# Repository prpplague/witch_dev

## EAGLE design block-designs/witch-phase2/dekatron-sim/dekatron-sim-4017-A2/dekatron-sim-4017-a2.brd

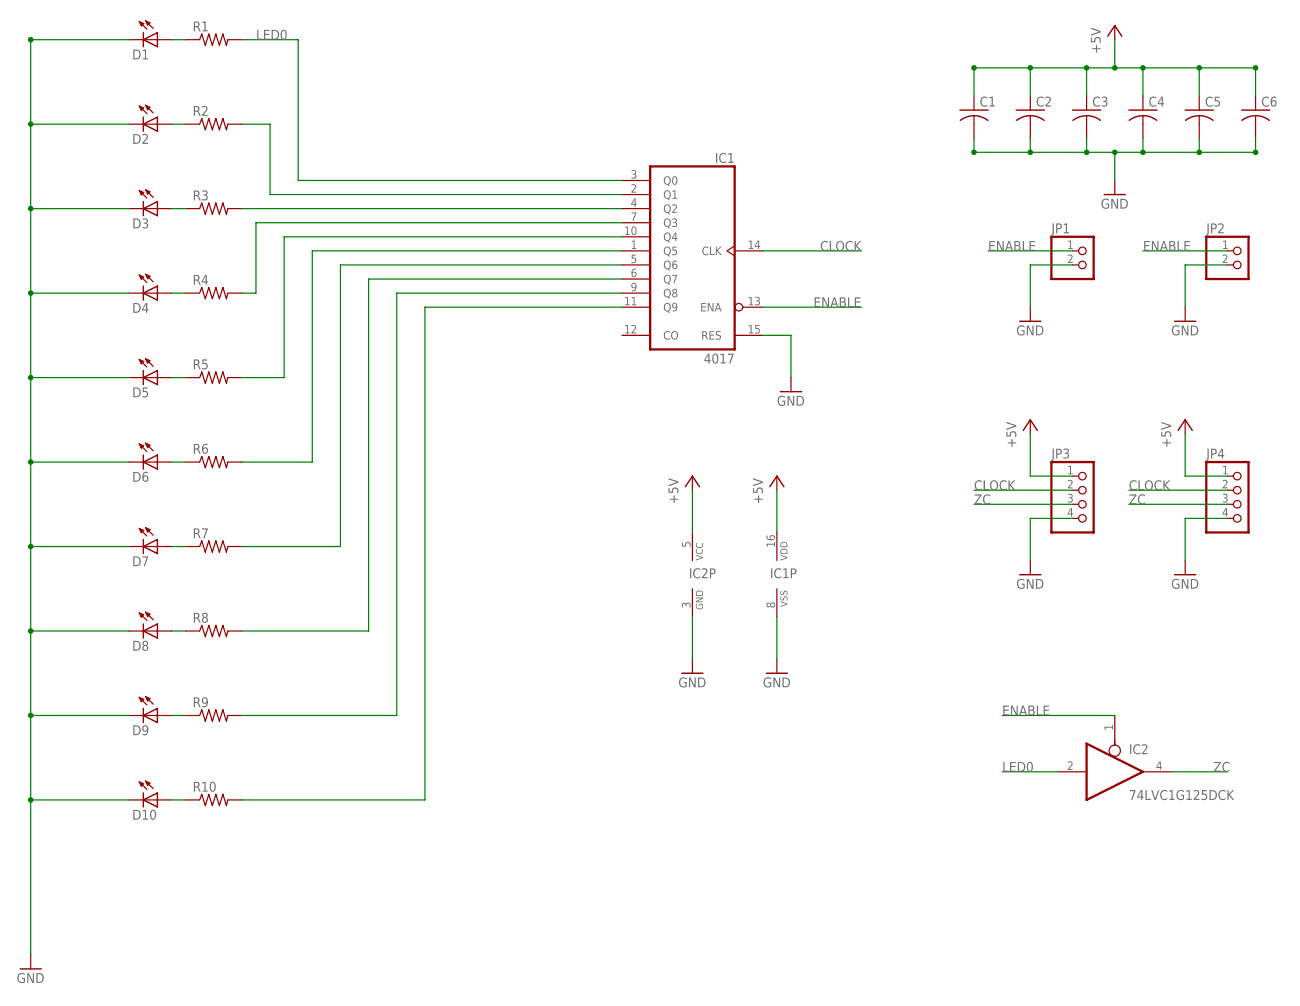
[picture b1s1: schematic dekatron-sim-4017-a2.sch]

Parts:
C1, C2, C3, C4, C5, C6: C-USC0805; C0805
D1, D2, D3, D4, D5, D6, D7, D8, D9, D10: RED; CHIP-LED0603
IC1: 4017; TSSOP16
IC2: 74LVC1G125DCK; SC70-5
JP1, JP2: PINHD-1X2; 1X02
JP3, JP4: PINHD-1X4; 1X04
R1, R2, R3, R4, R5, R6, R7, R8, R9, R10: R-US_R0603; R0603

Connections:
+5V: C1.1, C2.1, C3.1, C4.1, C5.1, C6.1, IC1.16 (VDD), IC2.5 (VCC), JP3.1, JP4.1
CLOCK: IC1.14 (CLK), JP3.2, JP4.2
ENABLE: IC1.13 (ENA), IC2.1 (OE), JP1.1, JP2.1
GND: C1.2, C2.2, C3.2, C4.2, C5.2, C6.2, D1.C, D2.C, D3.C, D4.C, D5.C, D6.C, D7.C, D8.C, D9.C, D10.C, IC1.8 (VSS), IC1.15 (RES), IC2.3 (GND), JP1.2, JP2.2, JP3.4, JP4.4
LED0: IC1.3 (Q0), IC2.2 (I), R1.2
LED1: IC1.2 (Q1), R2.2
LED3: IC1.7 (Q3), R4.2
LED4: IC1.10 (Q4), R5.2
LED5: IC1.1 (Q5), R6.2
LED6: IC1.5 (Q6), R7.2
LED7: IC1.6 (Q7), R8.2
LED8: IC1.9 (Q8), R9.2
LED9: IC1.11 (Q9), R10.2
unnamed: IC1.4 (Q2), R3.2
unnamed: D10.A, R10.1
unnamed: D9.A, R9.1
unnamed: D8.A, R8.1
unnamed: D7.A, R7.1
unnamed: D6.A, R6.1
unnamed: D5.A, R5.1
unnamed: D4.A, R4.1
unnamed: D3.A, R3.1
unnamed: D2.A, R2.1
unnamed: D1.A, R1.1
ZC: IC2.4 (O), JP3.3, JP4.3

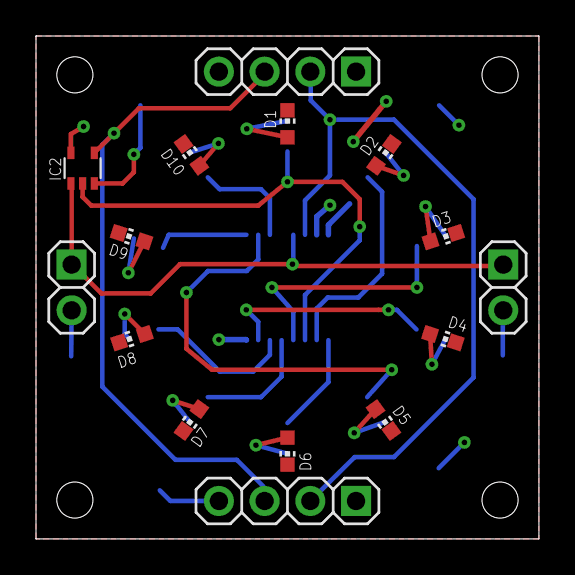
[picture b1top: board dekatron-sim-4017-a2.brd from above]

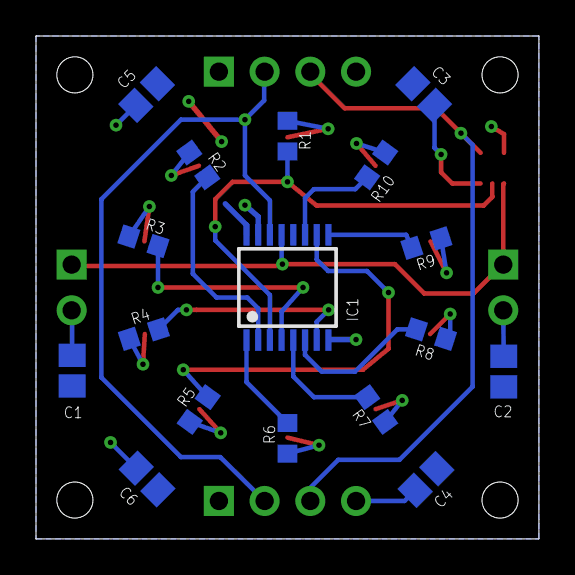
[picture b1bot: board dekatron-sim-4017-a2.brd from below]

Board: 2 copper layers, 27.9 x 27.9 mm, 32 parts (17 on the bottom side), 25 nets.

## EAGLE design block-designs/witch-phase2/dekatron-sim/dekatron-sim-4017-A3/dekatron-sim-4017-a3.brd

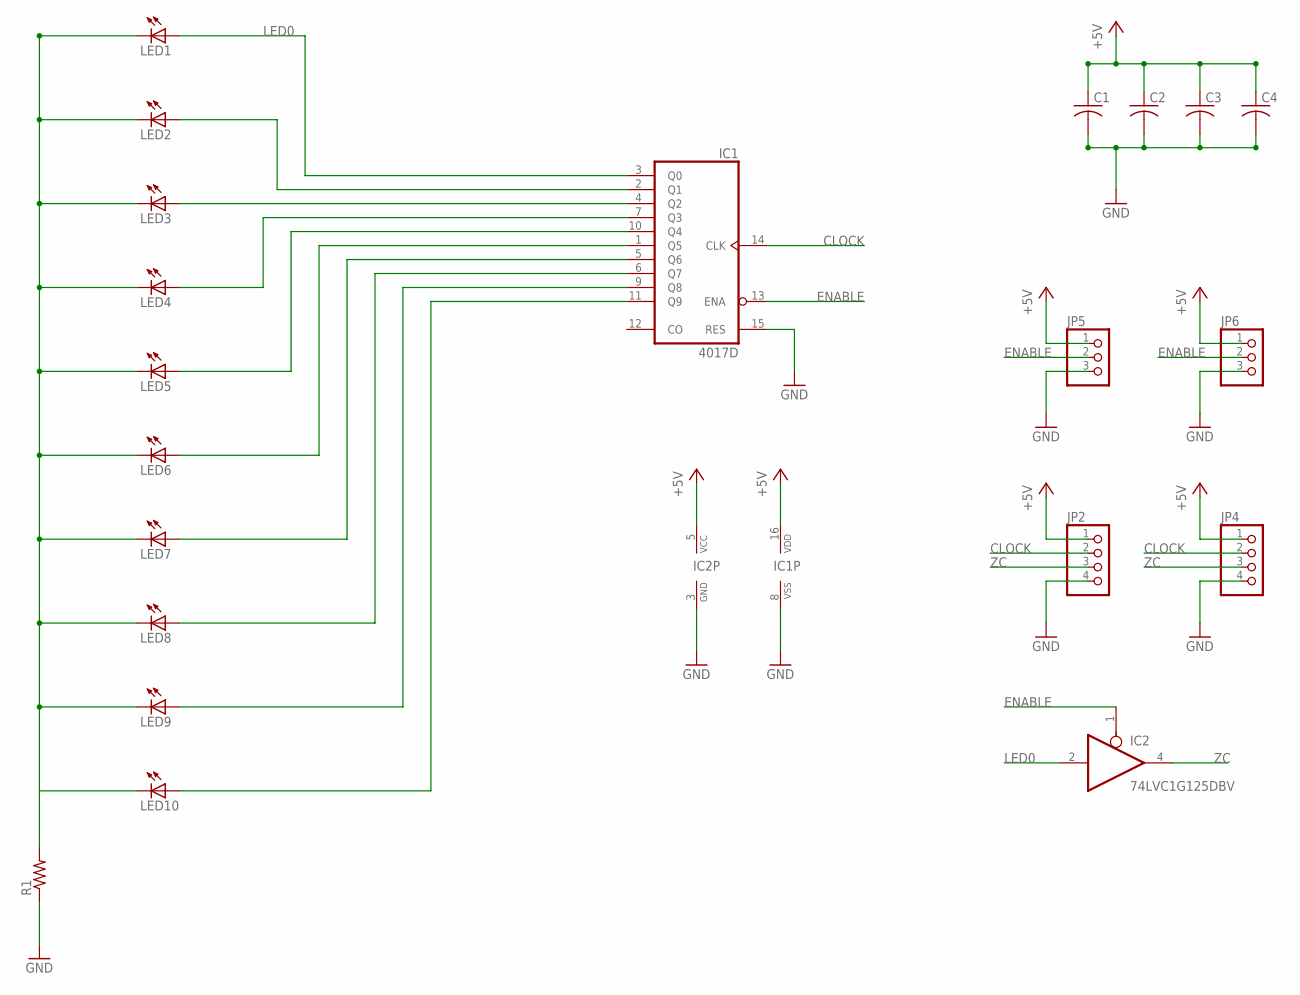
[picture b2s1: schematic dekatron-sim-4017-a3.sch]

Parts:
C1, C2, C3, C4: C-USC0805; C0805
IC1: 4017D; SO16
IC2: 74LVC1G125DBV; SOT23-5
JP2, JP4: PINHD-1X4; 1X04
JP5, JP6: PINHD-1X3; 1X03
LED1, LED2, LED3, LED4, LED5, LED6, LED7, LED8, LED9, LED10: RED; CHIP-LED0805
R1: R-US_R0805; R0805

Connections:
+5V: C1.1, C2.1, C3.1, C4.1, IC1.16 (VDD), IC2.5 (VCC), JP2.1, JP4.1, JP5.1, JP6.1
CLOCK: IC1.14 (CLK), JP2.2, JP4.2
ENABLE: IC1.13 (ENA), IC2.1 (OE), JP5.2, JP6.2
GND: C1.2, C2.2, C3.2, C4.2, IC1.8 (VSS), IC1.15 (RES), IC2.3 (GND), JP2.4, JP4.4, JP5.3, JP6.3, R1.1
LED0: IC1.3 (Q0), IC2.2 (I), LED1.A
LED1: IC1.2 (Q1), LED2.A
LED3: IC1.7 (Q3), LED4.A
LED4: IC1.10 (Q4), LED5.A
LED5: IC1.1 (Q5), LED6.A
LED6: IC1.5 (Q6), LED7.A
LED7: IC1.6 (Q7), LED8.A
LED8: IC1.9 (Q8), LED9.A
LED9: IC1.11 (Q9), LED10.A
LED_SINK: LED1.C, LED2.C, LED3.C, LED4.C, LED5.C, LED6.C, LED7.C, LED8.C, LED9.C, LED10.C, R1.2
unnamed: IC1.4 (Q2), LED3.A
ZC: IC2.4 (O), JP2.3, JP4.3

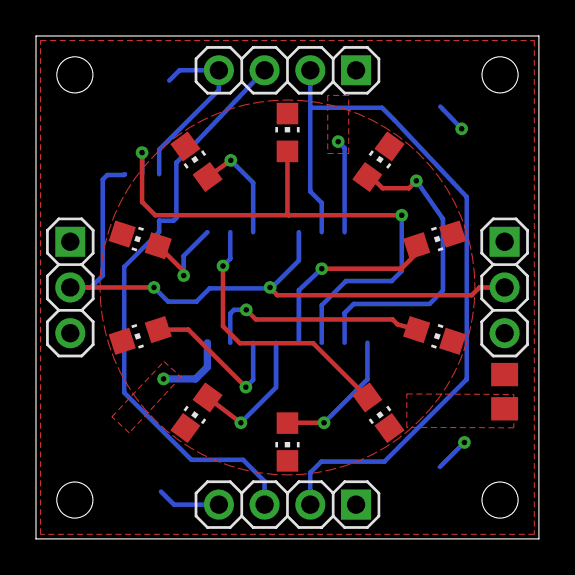
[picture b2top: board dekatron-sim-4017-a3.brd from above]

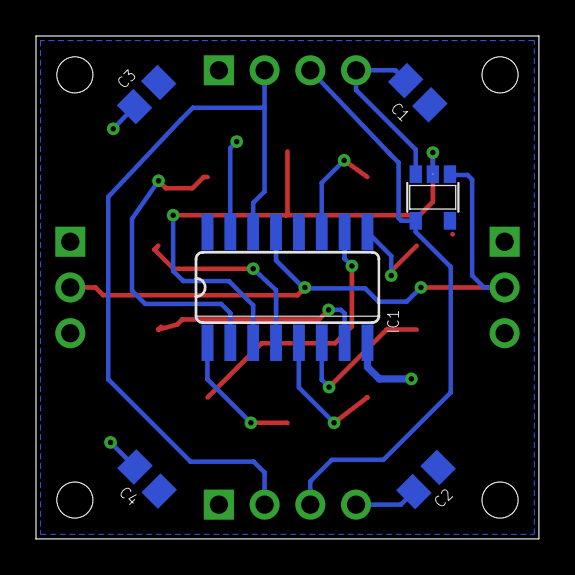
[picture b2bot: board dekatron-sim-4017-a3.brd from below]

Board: 2 copper layers, 27.9 x 27.9 mm, 21 parts (6 on the bottom side), 16 nets.

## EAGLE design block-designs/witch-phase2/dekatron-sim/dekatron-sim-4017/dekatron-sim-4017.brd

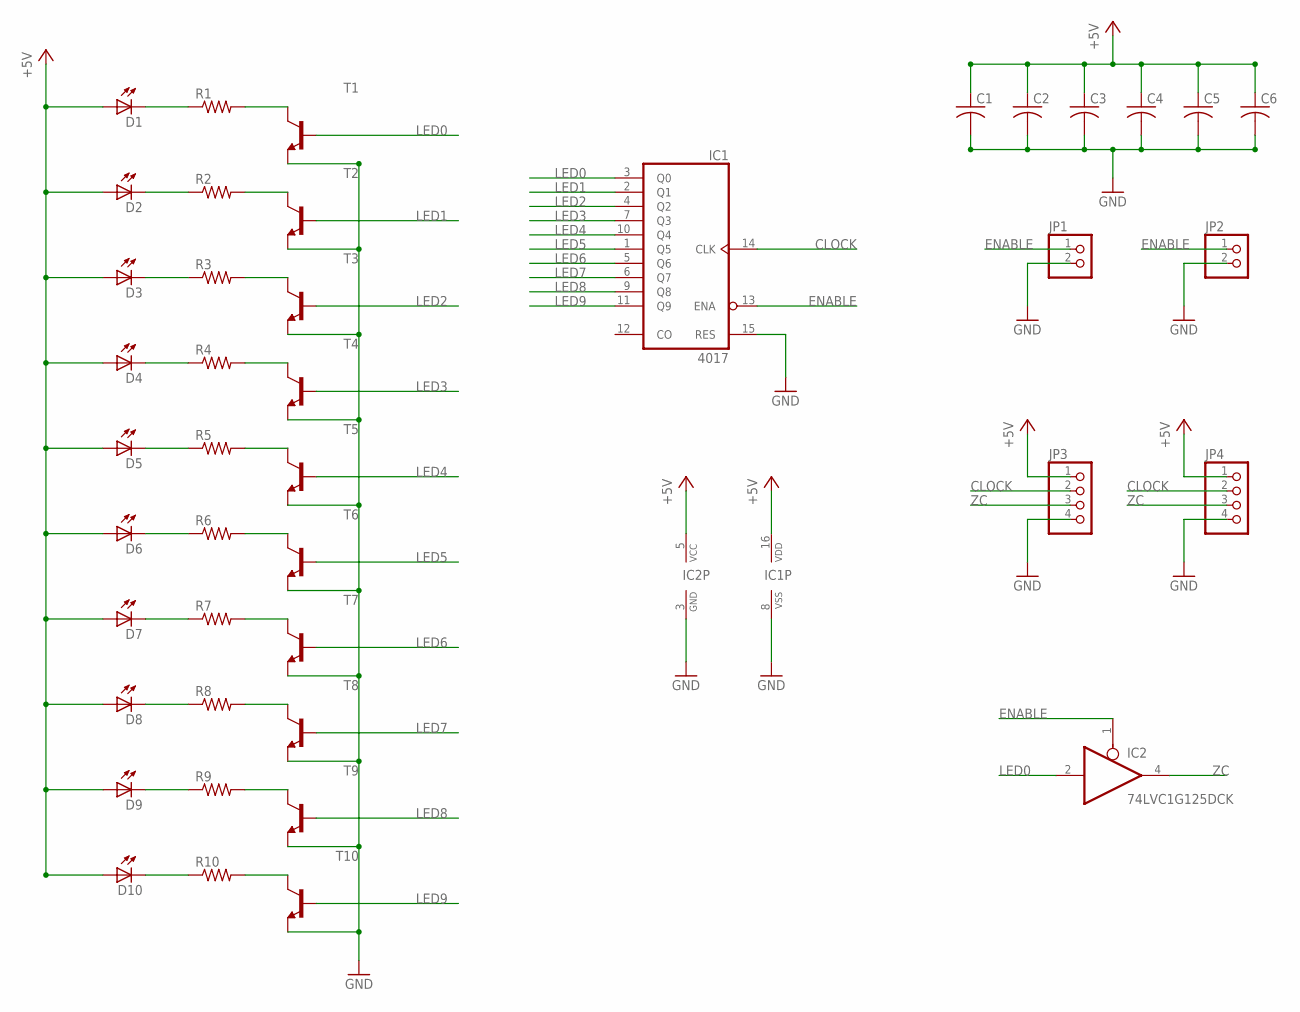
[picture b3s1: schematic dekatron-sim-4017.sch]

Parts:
C1, C2, C3, C4, C5, C6: C-USC0805; C0805
D1, D2, D3, D4, D5, D6, D7, D8, D9, D10: RED; CHIP-LED0603
IC1: 4017; TSSOP16
IC2: 74LVC1G125DCK; SC70-5
JP1, JP2: PINHD-1X2; 1X02
JP3, JP4: PINHD-1X4; 1X04
R1, R2, R3, R4, R5, R6, R7, R8, R9, R10: R-US_R0603; R0603
T1, T2, T3, T4, T5, T6, T7, T8, T9, T10: MMBT2222ALT1-NPN-SOT23-BEC; SOT23-BEC

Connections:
+5V: C1.1, C2.1, C3.1, C4.1, C5.1, C6.1, D1.A, D2.A, D3.A, D4.A, D5.A, D6.A, D7.A, D8.A, D9.A, D10.A, IC1.16 (VDD), IC2.5 (VCC), JP3.1, JP4.1
CLOCK: IC1.14 (CLK), JP3.2, JP4.2
ENABLE: IC1.13 (ENA), IC2.1 (OE), JP1.1, JP2.1
GND: C1.2, C2.2, C3.2, C4.2, C5.2, C6.2, IC1.8 (VSS), IC1.15 (RES), IC2.3 (GND), JP1.2, JP2.2, JP3.4, JP4.4, T1.E, T2.E, T3.E, T4.E, T5.E, T6.E, T7.E, T8.E, T9.E, T10.E
LED0: IC1.3 (Q0), IC2.2 (I), T1.B
LED1: IC1.2 (Q1), T2.B
LED2: IC1.4 (Q2), T3.B
LED3: IC1.7 (Q3), T4.B
LED4: IC1.10 (Q4), T5.B
LED5: IC1.1 (Q5), T6.B
LED6: IC1.5 (Q6), T7.B
LED7: IC1.6 (Q7), T8.B
LED8: IC1.9 (Q8), T9.B
LED9: IC1.11 (Q9), T10.B
unnamed: R10.2, T10.C
unnamed: R9.2, T9.C
unnamed: R8.2, T8.C
unnamed: D10.C, R10.1
unnamed: D9.C, R9.1
unnamed: D8.C, R8.1
unnamed: D7.C, R7.1
unnamed: R7.2, T7.C
unnamed: D6.C, R6.1
unnamed: R6.2, T6.C
unnamed: D5.C, R5.1
unnamed: R5.2, T5.C
unnamed: D4.C, R4.1
unnamed: R4.2, T4.C
unnamed: D3.C, R3.1
unnamed: R3.2, T3.C
unnamed: D2.C, R2.1
unnamed: R2.2, T2.C
unnamed: D1.C, R1.1
unnamed: R1.2, T1.C
ZC: IC2.4 (O), JP3.3, JP4.3

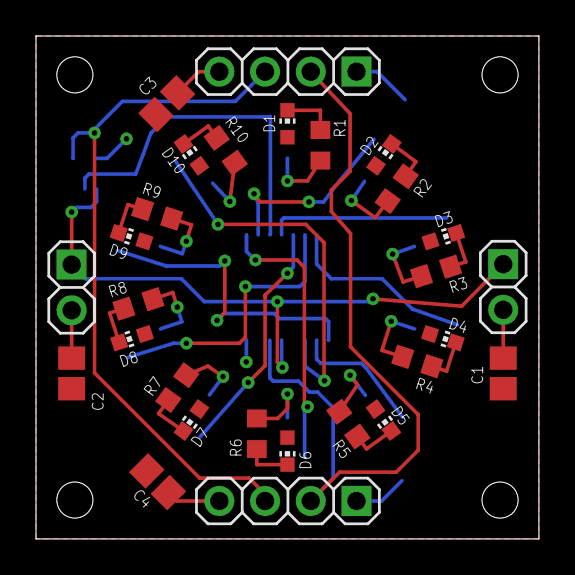
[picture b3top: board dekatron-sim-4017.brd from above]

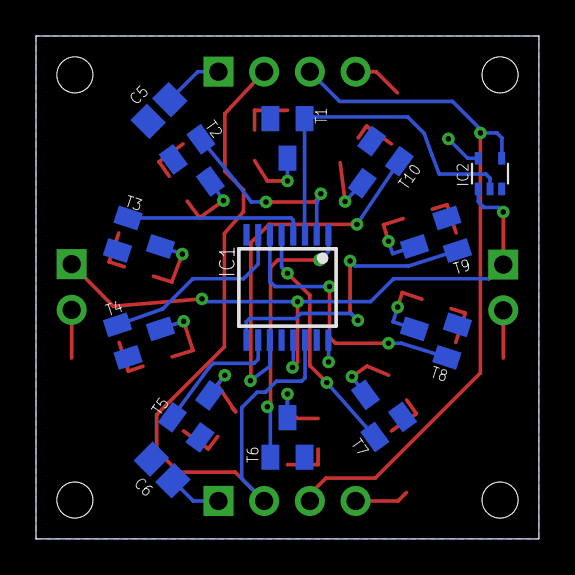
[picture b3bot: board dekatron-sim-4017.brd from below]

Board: 2 copper layers, 27.9 x 27.9 mm, 42 parts (14 on the bottom side), 35 nets.

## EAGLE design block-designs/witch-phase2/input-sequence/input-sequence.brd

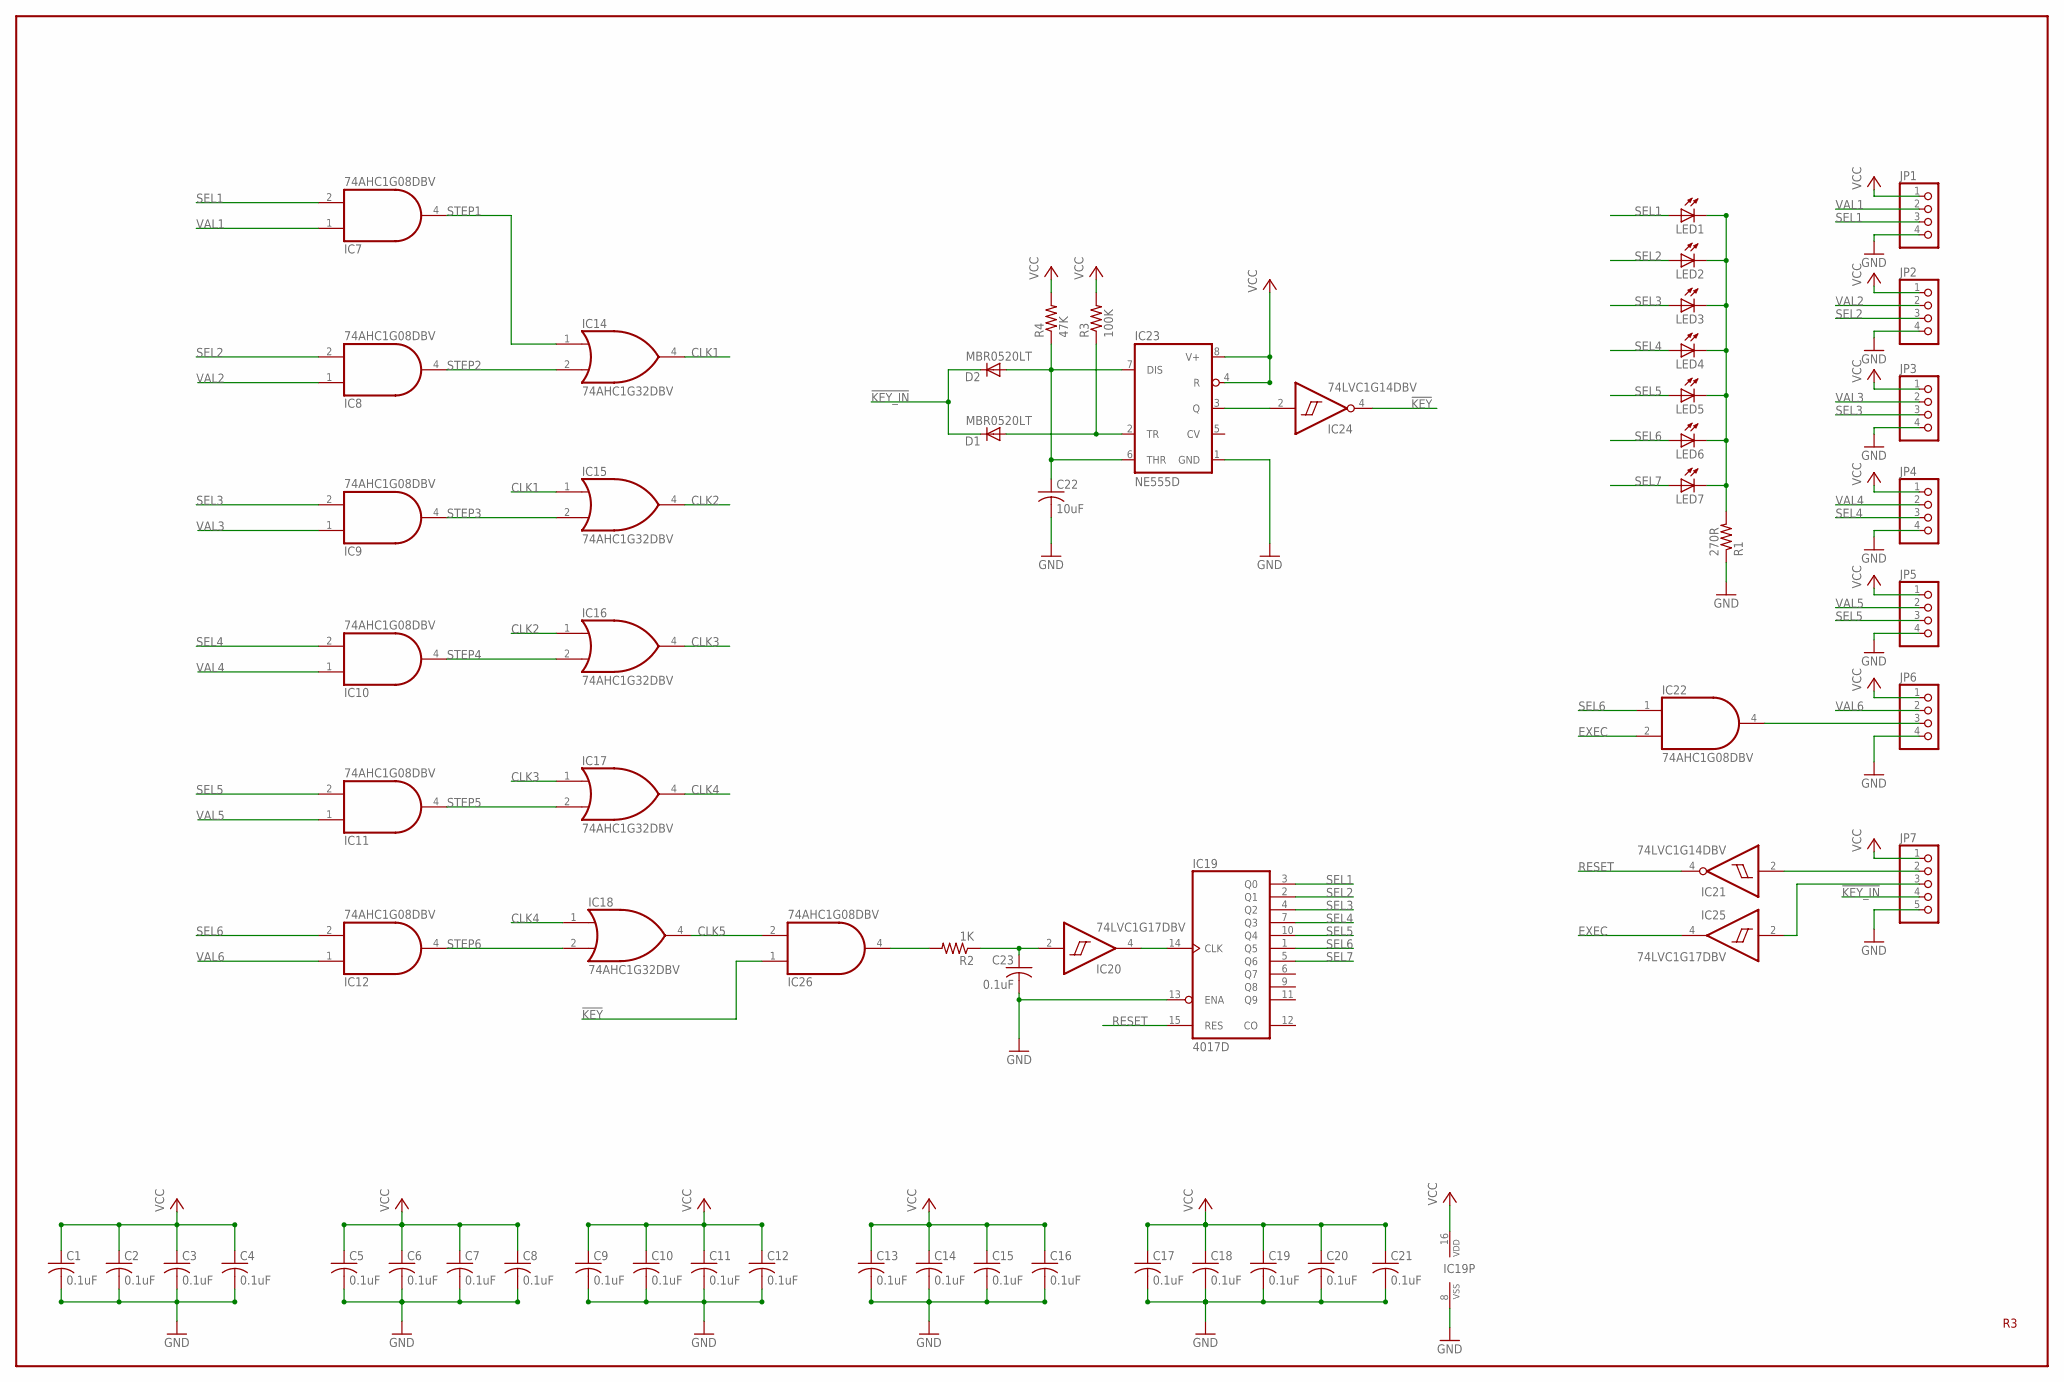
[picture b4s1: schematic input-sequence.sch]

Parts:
C1, C2, C3, C4, C5, C6, C7, C8, C9, C10, C11, C12, C13, C14, C15, C16, C17, C18, C19, C20, C21, C23: 0.1uF; C0603
C22: 10uF; C0805
D1, D2: MBR0520LT; SOD123
IC7, IC8, IC9, IC10, IC11, IC12, IC22, IC26: 74AHC1G08DBV; SOT23-5
IC14, IC15, IC16, IC17, IC18: 74AHC1G32DBV; SOT23-5
IC19: 4017D; SO16
IC20, IC25: 74LVC1G17DBV; SOT23-5
IC21, IC24: 74LVC1G14DBV; SOT23-5
IC23: NE555D; SO08
JP1, JP2, JP3, JP4, JP5, JP6: PINHD-1X4; 1X04
JP7: PINHD-1X5; 1X05
LED1, LED2, LED3, LED4, LED5, LED6, LED7: RED; CHIP-LED0805
R1: 270R; R0805
R2: 1K; R0805
R3: 100K; R0805
R4: 47K; R0805

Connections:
!CLEAR: IC21.2 (I), JP7.2
!KEY: IC24.4 (O), IC26.1 (I0)
!KEY_IN: D1.C, D2.C, JP7.4
CLK1: IC14.4 (O), IC15.1 (I0)
CLK2: IC15.4 (O), IC16.1 (I0)
CLK3: IC16.4 (O), IC17.1 (I0)
CLK4: IC17.4 (O), IC18.1 (I0)
CLK5: IC18.4 (O), IC26.2 (I1)
EXEC: IC22.2 (I1), IC25.4 (O)
GND: C1.2, C2.2, C3.2, C4.2, C5.2, C6.2, C7.2, C8.2, C9.2, C10.2, C11.2, C12.2, C13.2, C14.2, C15.2, C16.2, C17.2, C18.2, C19.2, C20.2, C21.2, C22.2, C23.2, IC7.3 (GND), IC8.3 (GND), IC9.3 (GND), IC10.3 (GND), IC11.3 (GND), IC12.3 (GND), IC14.3 (GND), IC15.3 (GND), IC16.3 (GND), IC17.3 (GND), IC18.3 (GND), IC19.8 (VSS), IC19.13 (ENA), IC20.3 (GND), IC21.3 (GND), IC22.3 (GND), IC23.1 (GND), IC24.3 (GND), IC25.3 (GND), IC26.3 (GND), JP1.4, JP2.4, JP3.4, JP4.4, JP5.4, JP6.4, JP7.5, R1.1
LED_SINK: LED1.C, LED2.C, LED3.C, LED4.C, LED5.C, LED6.C, LED7.C, R1.2
unnamed: IC22.4 (O), JP6.3
unnamed: IC19.14 (CLK), IC20.4 (O)
unnamed: C22.1, D2.A, IC23.6 (THR), IC23.7 (DIS), R4.1
unnamed: D1.A, IC23.2 (TR), R3.1
unnamed: IC23.3 (Q), IC24.2 (I)
unnamed: IC25.2 (I), JP7.3
unnamed: C23.1, IC20.2 (I), R2.1
unnamed: IC26.4 (O), R2.2
RESET: IC19.15 (RES), IC21.4 (O)
SEL1: IC7.2 (I1), IC19.3 (Q0), JP1.3, LED1.A
SEL2: IC8.2 (I1), IC19.2 (Q1), JP2.3, LED2.A
SEL3: IC9.2 (I1), IC19.4 (Q2), JP3.3, LED3.A
SEL4: IC10.2 (I1), IC19.7 (Q3), JP4.3, LED4.A
SEL5: IC11.2 (I1), IC19.10 (Q4), JP5.3, LED5.A
SEL6: IC12.2 (I1), IC19.1 (Q5), IC22.1 (I0), LED6.A
SEL7: IC19.5 (Q6), LED7.A
STEP1: IC7.4 (O), IC14.1 (I0)
STEP2: IC8.4 (O), IC14.2 (I1)
STEP3: IC9.4 (O), IC15.2 (I1)
STEP4: IC10.4 (O), IC16.2 (I1)
STEP5: IC11.4 (O), IC17.2 (I1)
STEP6: IC12.4 (O), IC18.2 (I1)
VAL1: IC7.1 (I0), JP1.2
VAL2: IC8.1 (I0), JP2.2
VAL3: IC9.1 (I0), JP3.2
VAL4: IC10.1 (I0), JP4.2
VAL5: IC11.1 (I0), JP5.2
VAL6: IC12.1 (I0), JP6.2
VCC: C1.1, C2.1, C3.1, C4.1, C5.1, C6.1, C7.1, C8.1, C9.1, C10.1, C11.1, C12.1, C13.1, C14.1, C15.1, C16.1, C17.1, C18.1, C19.1, C20.1, C21.1, IC7.5 (VCC), IC8.5 (VCC), IC9.5 (VCC), IC10.5 (VCC), IC11.5 (VCC), IC12.5 (VCC), IC14.5 (VCC), IC15.5 (VCC), IC16.5 (VCC), IC17.5 (VCC), IC18.5 (VCC), IC19.16 (VDD), IC20.5 (VCC), IC21.5 (VCC), IC22.5 (VCC), IC23.4 (R), IC23.8 (V+), IC24.5 (VCC), IC25.5 (VCC), IC26.5 (VCC), JP1.1, JP2.1, JP3.1, JP4.1, JP5.1, JP6.1, JP7.1, R3.2, R4.2

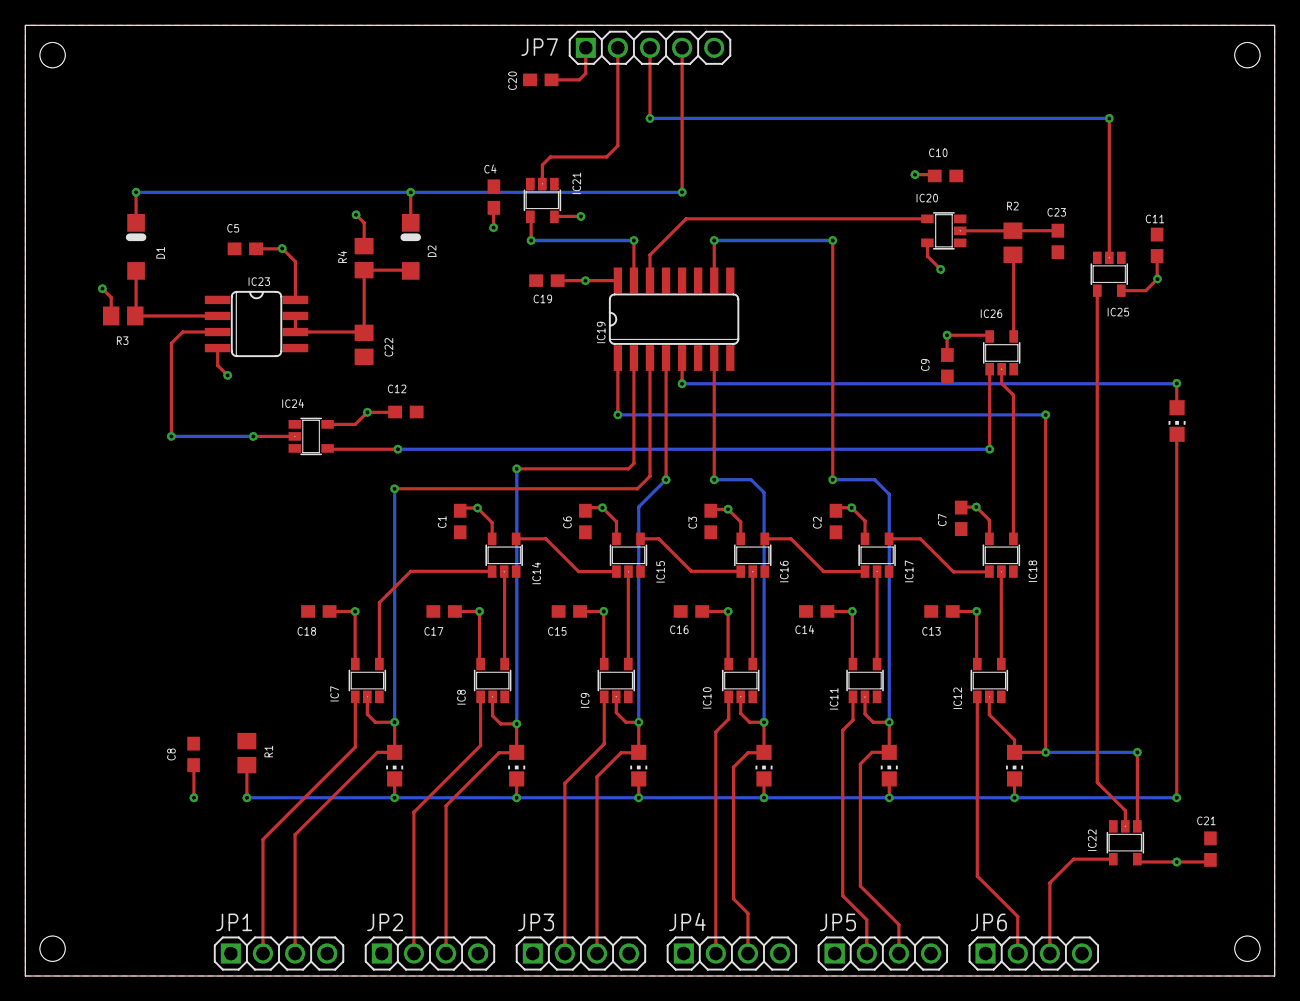
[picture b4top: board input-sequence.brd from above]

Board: 2 copper layers, 98.8 x 75.2 mm, 62 parts (0 on the bottom side), 40 nets.

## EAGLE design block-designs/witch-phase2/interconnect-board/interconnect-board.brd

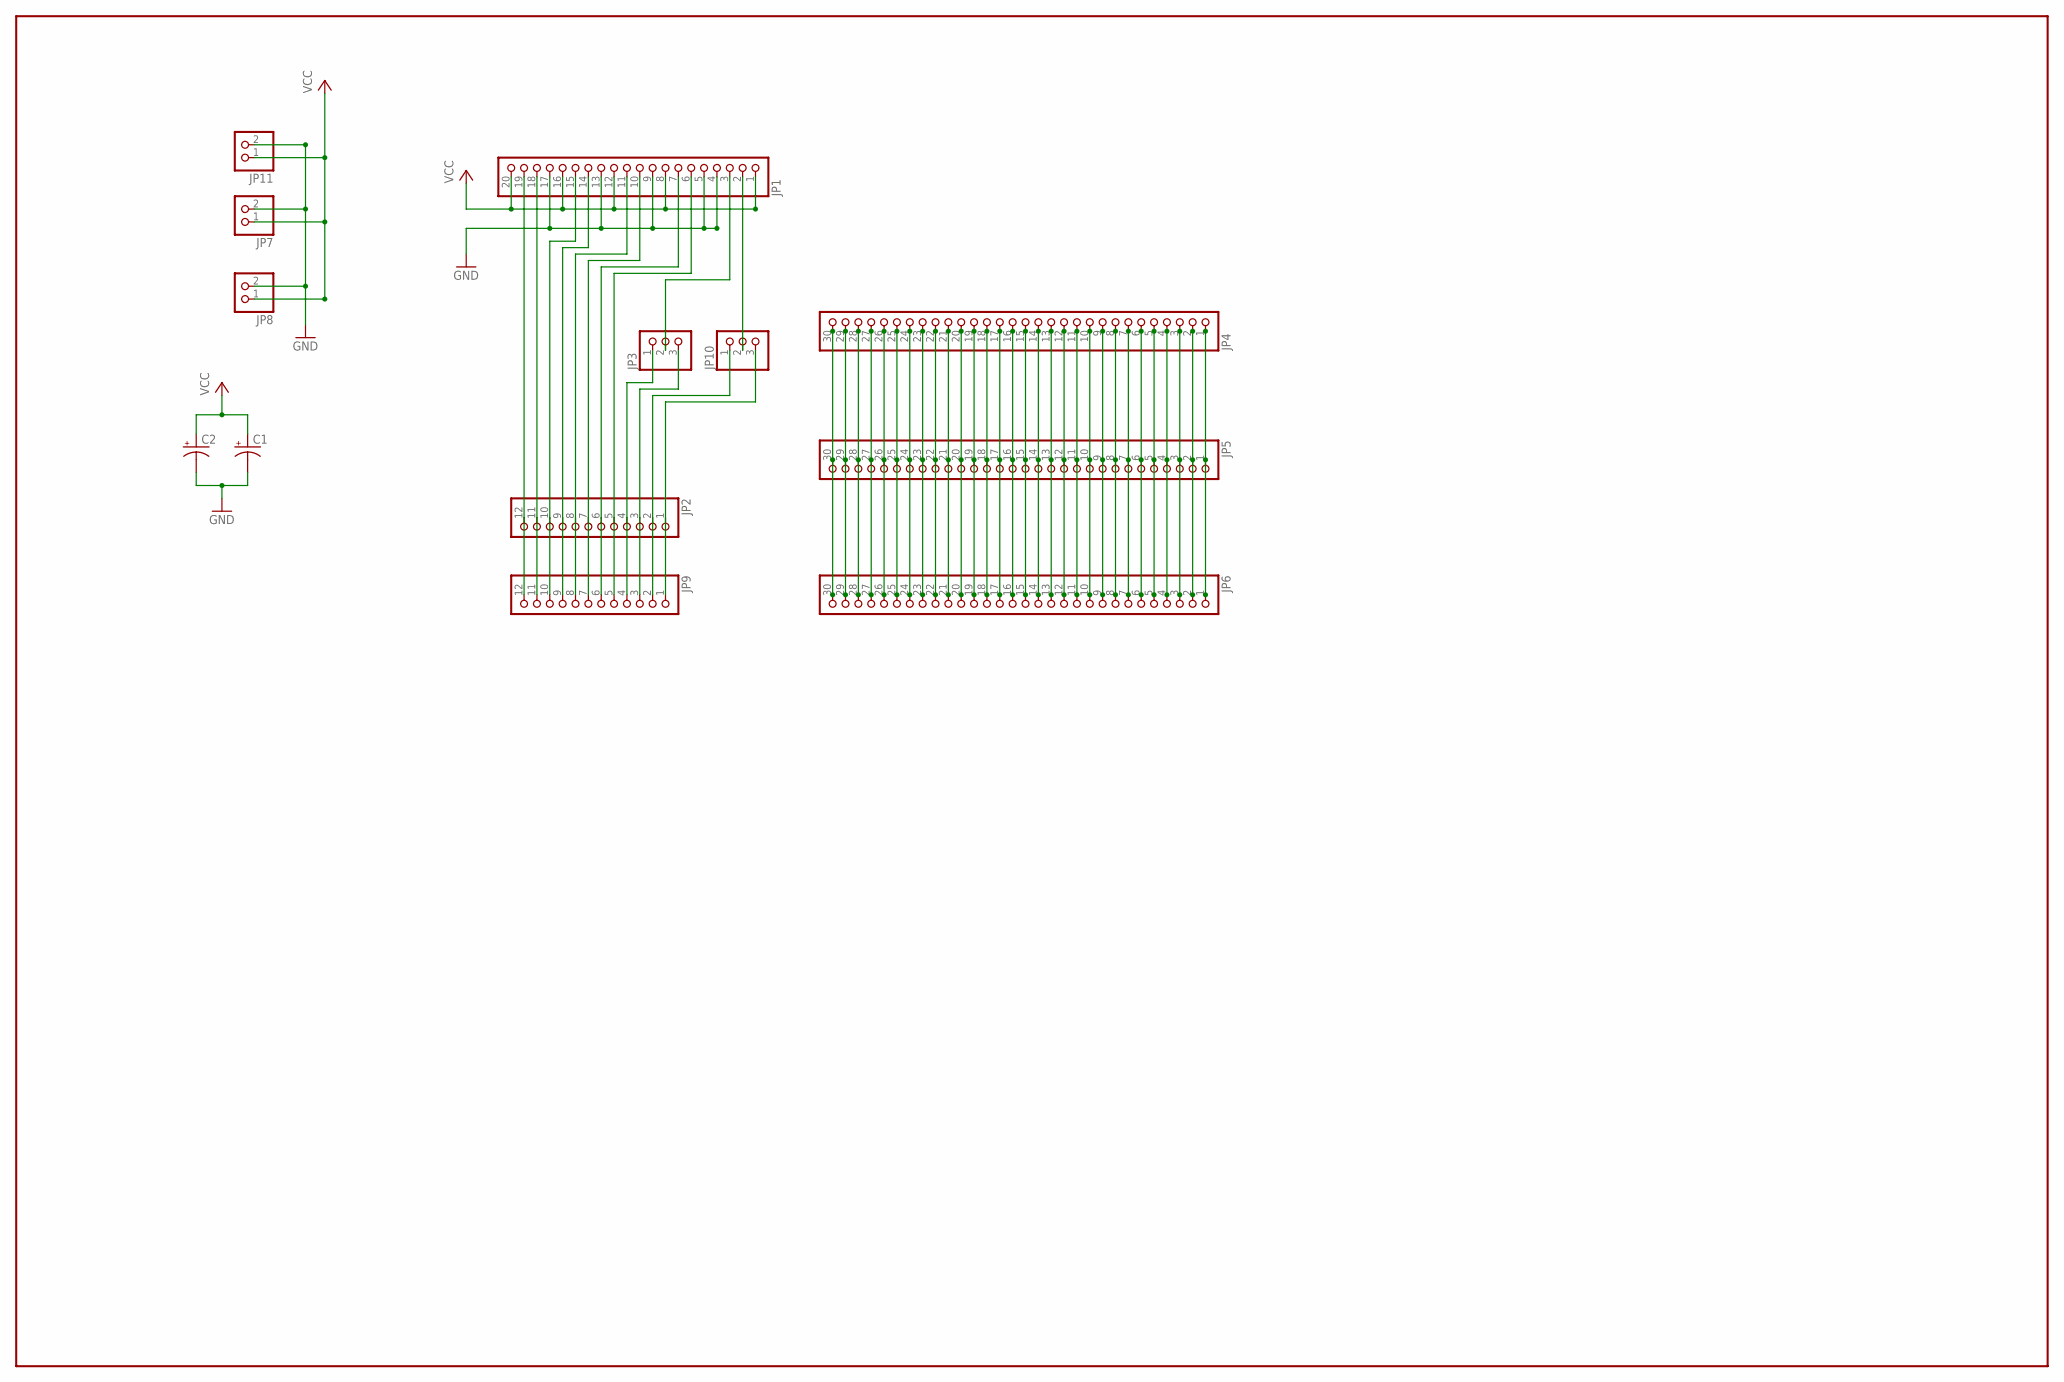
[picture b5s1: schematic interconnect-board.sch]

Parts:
C1, C2: CPOL-USE15-6AXIAL; E15-6
JP1: PINHD-1X20; 1X20
JP2, JP9: PINHD-1X12; 1X12
JP3, JP10: PINHD-1X3; 1X03
JP4, JP5, JP6: PINHD-1X30; 1X30
JP7, JP8, JP11: PINHD-1X2; 1X02

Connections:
GND: C1.-, C2.-, JP1.4, JP1.5, JP1.9, JP1.13, JP1.17, JP7.2, JP8.2, JP11.2
unnamed: JP4.30, JP5.30, JP6.30
unnamed: JP4.29, JP5.29, JP6.29
unnamed: JP4.28, JP5.28, JP6.28
unnamed: JP4.27, JP5.27, JP6.27
unnamed: JP4.26, JP5.26, JP6.26
unnamed: JP4.25, JP5.25, JP6.25
unnamed: JP4.24, JP5.24, JP6.24
unnamed: JP4.23, JP5.23, JP6.23
unnamed: JP4.22, JP5.22, JP6.22
unnamed: JP4.21, JP5.21, JP6.21
unnamed: JP4.20, JP5.20, JP6.20
unnamed: JP4.19, JP5.19, JP6.19
unnamed: JP4.18, JP5.18, JP6.18
unnamed: JP4.17, JP5.17, JP6.17
unnamed: JP4.16, JP5.16, JP6.16
unnamed: JP4.15, JP5.15, JP6.15
unnamed: JP4.14, JP5.14, JP6.14
unnamed: JP4.13, JP5.13, JP6.13
unnamed: JP4.12, JP5.12, JP6.12
unnamed: JP4.11, JP5.11, JP6.11
unnamed: JP4.10, JP5.10, JP6.10
unnamed: JP4.9, JP5.9, JP6.9
unnamed: JP4.8, JP5.8, JP6.8
unnamed: JP4.7, JP5.7, JP6.7
unnamed: JP4.6, JP5.6, JP6.6
unnamed: JP4.5, JP5.5, JP6.5
unnamed: JP4.4, JP5.4, JP6.4
unnamed: JP4.3, JP5.3, JP6.3
unnamed: JP4.2, JP5.2, JP6.2
unnamed: JP4.1, JP5.1, JP6.1
unnamed: JP1.19, JP2.12, JP9.12
unnamed: JP1.18, JP2.11, JP9.11
unnamed: JP1.15, JP2.10, JP9.10
unnamed: JP1.14, JP2.9, JP9.9
unnamed: JP1.11, JP2.8, JP9.8
unnamed: JP1.10, JP2.7, JP9.7
unnamed: JP1.7, JP2.6, JP9.6
unnamed: JP1.6, JP2.5, JP9.5
unnamed: JP2.4, JP3.1, JP9.4
unnamed: JP2.3, JP3.3, JP9.3
unnamed: JP2.2, JP9.2, JP10.1
unnamed: JP1.3, JP3.2
unnamed: JP1.2, JP10.2
unnamed: JP2.1, JP9.1, JP10.3
VCC: C1.+, C2.+, JP1.1, JP1.8, JP1.12, JP1.16, JP1.20, JP7.1, JP8.1, JP11.1

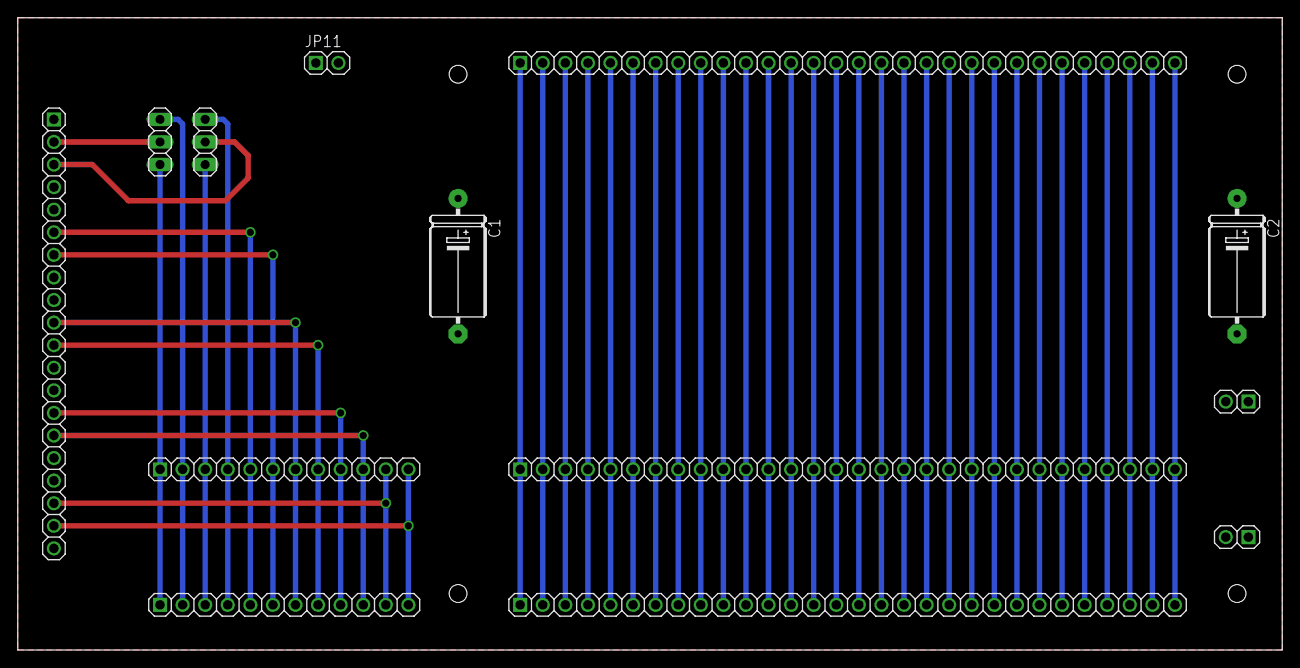
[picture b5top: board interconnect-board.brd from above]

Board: 2 copper layers, 142.2 x 71.1 mm, 13 parts (0 on the bottom side), 46 nets.
